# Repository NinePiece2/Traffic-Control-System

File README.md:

# **Traffic Control System** 🚦  

## NOTE

This project has been archived and all deployments have been termianted. 
If you want to deploy the project use the docker compose file.

## Table of Contents
- [**Traffic Control System** 🚦](#traffic-control-system-)
  - [Table of Contents](#table-of-contents)
  - [Workflow Status](#workflow-status)
  - [Introduction \& Background](#introduction--background)
    - [Background](#background)
    - [Rationale](#rationale)
    - [Scope](#scope)
  - [Design Specifications](#design-specifications)
    - [Pedestrian Detection and Safety](#pedestrian-detection-and-safety)
    - [Real-Time Video Streaming](#real-time-video-streaming)
    - [Hand Drawn Schematic of the Physical Design](#hand-drawn-schematic-of-the-physical-design)
    - [Microservice Architecture Design Diagram](#microservice-architecture-design-diagram)
    - [Early Design Mockup](#early-design-mockup)
    - [Final Design Implementation](#final-design-implementation)
      - [User Login](#user-login)
      - [Available Signals](#available-signals)
      - [Incident Reports for a Traffic Light](#incident-reports-for-a-traffic-light)
      - [Live Traffic Light](#live-traffic-light)
      - [Accounts Page](#accounts-page)
    - [Physical Design Components](#physical-design-components)
      - [PCB Design Image](#pcb-design-image)
      - [Design Assembly Render](#design-assembly-render)
      - [Design Assembly Render Video](#design-assembly-render-video)
      - [Physical Design Photo](#physical-design-photo)
  - [Installing the Microservices](#installing-the-microservices)
  - [Client Install Instructions:](#client-install-instructions)
    - [Client Debugging](#client-debugging)

## Workflow Status

| Workflow | Status |
|----------|--------|
| CI MVC Application | |
| CI API Application |  |
| CI Video Application |  |
| CD MVC, API, and Video Applications |  |
| Client CI Pipeline |  |

## Introduction & Background

A **smart traffic control system** designed to efficiently manage and optimize traffic flow.

### Background
In the modern day, successfully controlling urban traffic in the city is a necessity due to the ever-increasing number of vehicles and, consequently, the need for pedestrian safety.  In considering the traffic control system, what comes to mind is its ability to handle complex, changing traffic conditions, communicate clearly, and be accessible to visually impaired pedestrians. Additionally, incorporating sophisticated monitoring and control features into these systems continues to pose a technical challenge.

A frequent drawback in previous designs was the dependence on RF-link communication, which imposed limitations regarding data transmission reliability and scalability. To overcome these limitations, this project shifts to utilizing WiFi communication, providing increased flexibility, greater bandwidth, and improved compatibility with contemporary web-oriented control systems.

### Rationale
When determining the core processing unit, the Raspberry Pi was selected with the vision of being capable of employing adaptable and affordable embedded systems. Some of the benefits of the Raspberry Pi include real-time data processing, streamlined integration with cameras and sensors, and effective communication through WiFi. This makes it a perfect option for projects that need both hardware management and software interaction.

The web technologies were chosen to offer an intuitive user interface for system supervision and management. A .NET MVC website was created, incorporating Microsoft Identity Framework for secure user login, allowing the traffic system managers to have remote access to the system. As a result, supervisors can easily change parameters, manually control traffic signals, and view stored camera data such as images and videos of traffic violations. The addition of video imaging features improves the dependability of the system by allowing for future footage examination, holding violators accountable.

### Scope
The prototype created in this project tackles essential elements of traffic management by emphasizing real-time regulation and accessibility components. The system comprises:

1.	Real-Time Traffic Management: Combining magnetic reed switches and pedestrian buttons enables adaptive modification of traffic signals according to the presence of vehicles and pedestrians.
2.	Pedestrian Support: Buttons to signal a pedestrian to cross safely. Additionally, chimes at the time of safe crossing to signal the visually impaired are included.
3.	Traffic Violation Surveillance: A CMOS camera records high-quality images of traffic infractions, with video recording capabilities available for immediate processing and storage.
4.	Remote Management: A prototype website, developed using .NET MVC, allows for secure manual traffic light operations and remote observation of violation information.

This project provides a scalable solution for traffic control issues by incorporating contemporary technologies and enhancing traditional models. Future versions can upgrade the system’s capabilities to incorporate sophisticated image recognition, cloud storage, and overall traffic management across the network.

---

## Design Specifications

The Traffic Light Control System is designed to improve traffic management and pedestrian safety while addressing modern urban mobility challenges. The system provides:
-	Accessibility for Visually Impaired Pedestrians: Auditory signals inform visually impaired individuals when it is safe to cross the street.
-	Traffic Violation Detection: The Traffic Light Control System uses pressure sensors in order to detect when a vehicle crosses an intersection under a red light. It also uses a camera to take a picture of the violator's license plate, and record it for further use.
-	Remote Control and Data Access: The system uses a user friendly GUI, which, when connected to the internet, allows for monitoring the intersection at real time. Other features include recording and storing violations, and also manually adjusting the lights using an override.
-	Operation Modes: The user can change  traffic signal timings in accordance to different times of the day. this is useful for when there is an unexpected scenario, or an increase or decrease in traffic.
-	Power and Processing Requirements: A 5V power supply supports a Raspberry Pi single-board computer. The Raspberry Pi's integrated GPIO pins are used to interface with sensors, cameras, and traffic signal components, making it a very easy to use platform for this application.

### Pedestrian Detection and Safety

The SSD-MobileNetV2-FPNLite model is used to properly identify and classify pedestrians, vehicles and other objects. Pytesseract is used to extract license plates from vehicles that have commited traffic violations. For pedestrian safety, buzzers are used to sound for when there is a traffic violation detected, which is used alongside a pressure sensor. Lastly, other audio beeps are used for when a pedestrian requests to cross, and then they are sounded to make both the pedestrian and driver alerted of the shortened signal timings.

### Real-Time Video Streaming

RTMP ensures smooth video streaming from the CMOS camera to the GUI. This allows the user to be able to control traffic remotely, and make any changes necessary. They can also monitor the live intersection, and look at recorded traffic violations, should they deem necessary.

### Hand Drawn Schematic of the Physical Design

### Microservice Architecture Design Diagram

.png)

### Early Design Mockup

### Final Design Implementation

#### User Login 

#### Available Signals

#### Incident Reports for a Traffic Light

#### Live Traffic Light

#### Accounts Page

### Physical Design Components

To make the physical design look cohesive, a custom Printed Circut Board was designed and manufactured to replicate an actual traffic light. The CAD and PCB design files are availabe <a href="https://github.com/NinePiece2/Traffic-Control-System/tree/master/CADFiles" target="_blank" rel="noopener noreferrer">here</a>. The CAD files were designed using Fusion 360 and the PCB was created using KiCAD.

#### PCB Design Image

#### Design Assembly Render

#### Design Assembly Render Video

<!-- <video src="images/Dual_Traffic_Light_Variant_2_Assembly_Render_v3_Animation_2.mp4" autoplay muted loop playsinline width="800"></video> -->

Click to download the video:

#### Physical Design Photo

---

## Installing the Microservices

Use ```docker-compose.yml``` and change the variables where applicable to allow the microservices to communicate with each other. Use SSL certificates as required. The `JWT_KEY` should be the same on all the services.

```docker-compose.yml```:

```yml
version: '3.8'

services:
  mvc:
    image: ninepiece2/traffic-control-system:mvc
    container_name: Traffic-Control-System
    ports:
      - "8443:8443"
    volumes:
      - /root/certs:/https:ro
    environment:
      - ASPNETCORE_URLS=https://*:8443;http://*:8080
      - ASPNETCORE_Kestrel__Certificates__Default__Path=/https/ssl.crt
      - ASPNETCORE_Kestrel__Certificates__Default__KeyPath=/https/ssl.key
      - ASPNETCORE_ENVIRONMENT=${ASPNETCORE_ENVIRONMENT}
      - SyncfusionLicense=${SyncfusionLicense}
      - BaseUrl=https://trafficcontrolsystem.romitsagu.com
      - VideoServiceURL=https://stream-trafficcontrolsystem.romitsagu.com
      - StreamServiceURL=https://stream1-trafficcontrolsystem.romitsagu.com
      - APIURL=https://api-trafficcontrolsystem.romitsagu.com
      - API_KEY=${JWT_Key}
    command: ["dotnet", "Traffic-Control-System.dll"]
    restart: always
  
  api:
    image: ninepiece2/traffic-control-system:api
    container_name: Traffic-Control-System-API
    ports:
      - "8445:8445"
    volumes:
      - /root/certs:/https:ro
    environment:
      - ASPNETCORE_URLS=https://*:8445;http://*:8080
      - ASPNETCORE_Kestrel__Certificates__Default__Path=/https/ssl.crt
      - ASPNETCORE_Kestrel__Certificates__Default__KeyPath=/https/ssl.key
      - ASPNETCORE_ENVIRONMENT=${ASPNETCORE_ENVIRONMENT}
      - StreamServiceURL=https://stream1-trafficcontrolsystem.romitsagu.com
      - JWT:Issuer=https://api-trafficcontrolsystem.romitsagu.com
      - JWT:Audience=https://api-trafficcontrolsystem.romitsagu.com
      - JWT:Key=${JWT_Key}
    command: ["dotnet", "Traffic-Control-System-API.dll"]
    restart: always

  video:
    image: ninepiece2/traffic-control-system:video
    container_name: Traffic-Control-System-Video
    ports:
      - "1935:1935"
      - "8446:8446"
    volumes:
      - /root/certs:/https:ro
    environment:
      - ASPNETCORE_URLS=https://*:8446;http://*:8080
      - ASPNETCORE_Kestrel__Certificates__Default__Path=/https/ssl.crt
      - ASPNETCORE_Kestrel__Certificates__Default__KeyPath=/https/ssl.key
      - ASPNETCORE_ENVIRONMENT=${ASPNETCORE_ENVIRONMENT}
      - JWT:Issuer=https://stream-trafficcontrolsystem.romitsagu.com
      - JWT:Audience=https://stream-trafficcontrolsystem.romitsagu.com
      - JWT:Key=${JWT_Key}
    command: ["dotnet", "Traffic-Control-System-Video.dll"]
    restart: always
```

## Client Install Instructions:

Run the following on a Raspberry Pi 5. This will install docker, docker compose and create a new folder with the ```docker-compose.yml``` file and a config file located under ```config/config.json```. After creating a new traffic light in the MVC application enter the outputed config values in the ```config/config.json``` file. Follow the instructions and run ```docker compose up -d```/```docker-compose up -d``` within the created folder to run the container and traffic light application.

```sh
curl -O https://raw.githubusercontent.com/NinePiece2/Traffic-Control-System/refs/heads/master/RaspPiPythonScripts/installer.sh && sudo bash installer.sh
```

### Client Debugging

If you enconuter:

```sh
OSError: [Errno 12] Cannot allocate memory
```

Go to the file `sudo nano /boot/firmware/config.txt`

Locate the line `dtoverlay=vc4-fkms-v3d` and change it to `dtoverlay=vc4-fkms-v3d,cma-256` and Restart the Raspberry Pi.

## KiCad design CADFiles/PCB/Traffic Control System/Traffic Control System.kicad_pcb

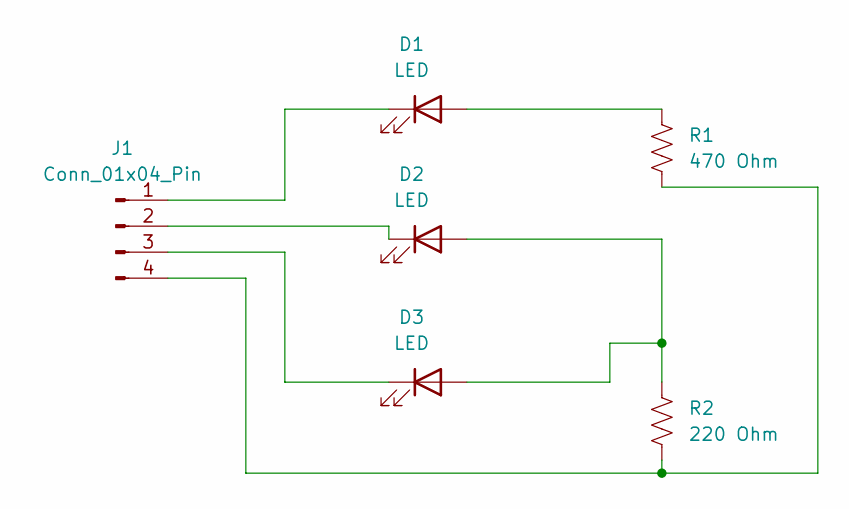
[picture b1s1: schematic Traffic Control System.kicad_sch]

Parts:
D1, D2, D3: LED; LED_D5.0mm_Clear
J1: Conn_01x04_Pin; SolderWire-0.25sqmm_1x04_P4.2mm_D0.65mm_OD1.7mm
R1: 470 Ohm; R_Box_L13.0mm_W4.0mm_P9.00mm
R2: 220 Ohm; R_Box_L13.0mm_W4.0mm_P9.00mm

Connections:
unnamed: D1.2 (A), R1.1
unnamed: D1.1 (K), J1.1
unnamed: D2.2 (A), D3.2 (A), R2.1
unnamed: D2.1 (K), J1.2
unnamed: D3.1 (K), J1.3
unnamed: J1.4, R1.2, R2.2

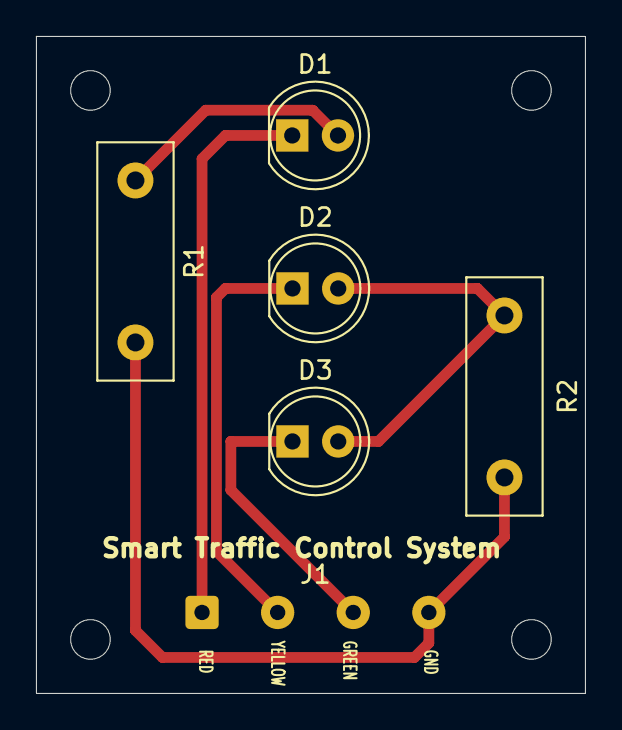
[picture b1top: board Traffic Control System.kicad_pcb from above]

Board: 2 copper layers, 30.5 x 36.5 mm, 6 parts (0 on the bottom side), 6 nets.

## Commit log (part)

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2024-10-03 Add .gitattributes and .gitignore.
2024-10-03 Add project files.
2024-10-03 Adding CI/CD
2024-10-03 Connect DB
2024-10-04 add README.md
2024-10-05 Small Changes
2024-10-05 Add Syncfusion and Admin Page
2024-10-06 Fix up admin users page
2024-10-08 Small Login Page Fixes
2024-10-09 Update Secondary Colour
2024-10-09 Add PowerSettings
2024-10-10 Add Email Service
2024-10-11 Add Confirmed User accounts and more Email Service Functionality
2024-10-12 Add approval/deny UI
2024-10-14 Add account approved logic
2024-10-16 Add Role Changes
2024-10-18 UI Improvements
2024-10-18 UI Improvements and Register Page Validation fixes
2024-10-18 Navbar Enhancements
2024-10-25 Add pi python test file
2024-10-25 Fix basic traffic light setup
2024-10-27 Add Websocket and video test
2024-10-27 Fix video issues
2024-10-27 add creations to dockerfile
2024-10-27 Try fix
2024-10-27 Add wget
2024-10-27 Try fix docker setup
2024-10-27 Try fix docker
2024-10-27 Fix docker
2024-10-27 Try to improve delay
2024-10-27 try to fix framerate
2024-10-27 Try to fix delay
2024-10-27 Try to fix framerate issues
2024-10-31 Use LiveStreamingServerNet for video streaming.
2024-10-31 Add python video streaming
2025-01-03 Add Seperate Microservices
2025-01-03 Fix build issues
2025-01-03 Try to fix publish
2025-01-03 Prune Images upon creation
2025-01-03 Try to fix build/publish issue
2025-01-03 Try to fix build/puiblsih
2025-01-03 Add missing file
2025-01-04 Try to fix video FFMpeg error
2025-01-08 Fix video streaming server
2025-01-12 Update URLs add add ClipController
2025-01-12 Update URLs
2025-01-13 Add Video Player demo
2025-01-13 Improved stream and video recording
2025-01-13 Add updated video stream
2025-01-13 Add initial FTP File Service
2025-01-13 Updated: The Signals Page
2025-01-14 Update ActiveSignals to use View TrafficSignals instead
2025-01-14 Update Video and MVC services
2025-01-16 Update .gitignore [no-ci]
2025-01-16 Make Clip Storage dependant on intersection
2025-01-16 Fix video upload issue
2025-01-16 Add Clips Uploader
2025-01-18 signalR test
2025-01-18 Add SignalR source
2025-01-18 python client for getting StreamClientKey using GET
2025-01-19 python client for get requests and StreamClientKey
2025-01-19 removal of file
2025-01-20 c# code for post requests and subsequent python code
2025-01-20 c# code for post requests and subsequent working python code
2025-01-20 Add Arshad Changes
2025-01-21 Fix Py Issue [no ci]
2025-01-22 Updateone
2025-01-22 Update Modal/Pop-Up
2025-01-23 Add Frontend for Video Streaming and Clip Viewing
2025-01-23 Fix SignalR merge issue
2025-01-23 Add Page Links
2025-01-29 Add Python Compose update
2025-01-29 Update python ci
2025-01-29 Fix and Test python CI
2025-01-30 Small Changes [no-ci]
2025-01-30 Update docker file for testing and installer
2025-01-30 Fix requirements
2025-01-30 Fix lgpio issue
2025-01-30 Fix gpiozero issue
2025-01-30 Fix Docker runtime issue
2025-01-30 Update Python Library
2025-01-30 Add missing requirements
2025-01-30 Add Webcam config
2025-01-31 Try to fix webcam issue
2025-01-31 Try to fix FFMpeg issue
2025-01-31 Try to fix FFMpeg Webcam issue
2025-01-31 Update [skip ci]
2025-01-31 Add manual CI option
2025-01-31 Fix CI picamera2 install issue
2025-01-31 Fix numpy dependency issue
2025-01-31 Update docker-compose.yml [skip ci]
2025-01-31 Clean up repos [skip ci]
2025-02-02 Small Update [skip ci]
2025-02-02 Update installer [skip ci]
2025-02-03 Fix Installer
2025-02-03 Fix Installer [skip ci]
2025-02-03 signal r update
2025-02-04 Update SignalR Receive message [skip ci]
2025-02-07 updating modal
2025-02-07 updateeee
2025-02-11 Edit table update
2025-02-11 Updated Index
2025-02-13 traffic controller for direction and time and python client
2025-02-13 traffic controller for direction and time and python client without bloat
2025-02-13 traffic controller for direction and time and python client without bloat updated
2025-02-13 removed dist
2025-02-13 Try to fix concurrent CI issue
2025-02-17 Add YOLO
2025-02-17 Use IMX500
2025-02-17 Update IMX500
2025-02-17 Update video
2025-02-17 Add IMX500 Object Detection and Test CI
2025-02-17 Remove unneeded entry in .gitignore
2025-02-17 Try to fix pip install issue
2025-02-18 Add Incident Detected Hook
2025-02-18 Add Table Of Contents
2025-02-18 README.md update
2025-02-18 Try to fix build error
2025-02-18 Client Update [skip ci]
2025-02-18 Add License Plate Detection
2025-02-18 Fix assets path
2025-02-18 Impove License Plate Detection
2025-02-18 Improve Clip Capture
2025-02-18 Add Tesseract OCR
2025-02-18 Fix folder upload
2025-02-18 Add Improve CI/CD for improved runtime
2025-02-18 Fix version issue
2025-02-18 Fix Pipeline README.md information
2025-02-18 Fix Video Framerate issue [skip ci]
2025-02-19 Improve Incident Reports Page
2025-02-19 UI Updates
2025-02-19 Add Filtering to Index
2025-02-19 Add Filtering and Sorting to Index Table
2025-02-19 Add Latest Violation
2025-02-22 Don't upload the original video
2025-02-22 Add better video autoplay and video sizing
2025-02-22 Try to fix unified deploy issue
2025-02-22 Try to fix deploy concurrency issue
2025-02-22 Improve Reports page videos
2025-02-23 Add persistant key database storage
2025-02-23 Remove unneeded import [skip ci]
2025-03-05 Final Update:
2025-03-06 Fix API Key issue [skip ci]
2025-03-06 Add PCB Files
2025-03-06 Add Gerber Output Files
2025-03-07 Update PCB
2025-03-07 Add Traffic Light Stand .step files
2025-03-08 Update GetDirectionAndTime()
2025-03-08 Add PedestrianWalkTime to API
2025-03-08 Add final PCB Fabrication Files
2025-03-10 Client Changes [skip ci]
2025-03-10 Update Device Control [skip ci]
2025-03-10 Update Server and Client SignalR Interfaces
2025-03-10 Update SignalR Server
2025-03-10 Add traffic light status passthrough
2025-03-10 Fix Colour Case Issue
2025-03-10 Use Classes Instead of IDs for timing spans
2025-03-10 Make SignalR connection more reliable
2025-03-10 Remove Unneded Comments
2025-03-10 Try to fix excesive console logs
2025-03-10 Improve UI/UX
2025-03-10 Add Buzzers and Revise Buttons [skip ci]
2025-03-10 Update Pedestrian Buttons [skip ci]
2025-03-10 Set Duy Cycle to 20% [skip ci]
2025-03-10 Update Buzzer and Pedestrian Logic [skip ci]
2025-03-10 Update Pedestrian Sounds
2025-03-11 Add missing method
2025-03-11 Fix Jingle Sounds
2025-03-11 Improve Buzzer Initialization [skip ci]
2025-03-11 Improve Buzzer Timings [skip ci]
2025-03-11 Add Button and Buzzer Stand
2025-03-11 Remove Unneeded Pages
2025-03-12 Update CAD Files
2025-03-13 Small Updates [skip ci]
2025-03-14 Add pressure sensing [skip ci]
2025-03-14 Fix double pin issue [skip ci]
2025-03-14 Add Getting Buzzer Volume and adding it tothe config
2025-03-14 Add Incident Detection [skip ci]
2025-03-14 Try to fix FFMpeg Issue [skip ci]
2025-03-14 Improve Pedestrian Button Mount
2025-04-04 Fix timing bug
2025-08-12 Add documentation
2025-08-13 Improve design specs
2025-09-23 Upgrade .NET SDK and runtime to version 9.0 across all projects and update dependencies
2025-09-23 Update workflow configurations to use 'ubuntu-latest' instead of 'self-hosted'
2025-09-23 deps(github-actions): bump docker/build-push-action from 5 to 6
    Bumps [docker/build-push-action](https://github.com/docker/build-push-action) from 5 to 6.
    - [Release notes](https://github.com/docker/build-push-action/releases)
    - [Commits](https://github.com/docker/build-push-action/compare/v5...v6)
    ---
    updated-dependencies:
    - dependency-name: docker/build-push-action
2025-09-23 deps(github-actions): bump actions/github-script from 6 to 8
    Bumps [actions/github-script](https://github.com/actions/github-script) from 6 to 8.
    - [Release notes](https://github.com/actions/github-script/releases)
    - [Commits](https://github.com/actions/github-script/compare/v6...v8)
    ---
    updated-dependencies:
    - dependency-name: actions/github-script
2025-10-01 deps(github-actions): bump peter-evans/repository-dispatch from 3 to 4
    Bumps [peter-evans/repository-dispatch](https://github.com/peter-evans/repository-dispatch) from 3 to 4.
    - [Release notes](https://github.com/peter-evans/repository-dispatch/releases)
    - [Commits](https://github.com/peter-evans/repository-dispatch/compare/v3...v4)
    ---
    updated-dependencies:
    - dependency-name: peter-evans/repository-dispatch
2025-11-20 deps(github-actions): bump actions/checkout from 5 to 6
    Bumps [actions/checkout](https://github.com/actions/checkout) from 5 to 6.
    - [Release notes](https://github.com/actions/checkout/releases)
    - [Changelog](https://github.com/actions/checkout/blob/main/CHANGELOG.md)
    - [Commits](https://github.com/actions/checkout/compare/v5...v6)
    ---
    updated-dependencies:
2026-02-05 deps(Traffic-Control-System): Bump the microsoft-dependencies group with 8 updates
    Bumps Microsoft.AspNetCore.DataProtection.EntityFrameworkCore from 9.0.9 to 9.0.12
    Bumps Microsoft.AspNetCore.Diagnostics.EntityFrameworkCore from 9.0.9 to 9.0.12
    Bumps Microsoft.AspNetCore.Identity.EntityFrameworkCore from 9.0.9 to 9.0.12
    Bumps Microsoft.AspNetCore.Identity.UI from 9.0.9 to 9.0.12
    Bumps Microsoft.EntityFrameworkCore.Sqlite from 9.0.9 to 9.0.12
    Bumps Microsoft.EntityFrameworkCore.SqlServer from 9.0.9 to 9.0.12
2026-02-05 deps(Traffic-Control-System): Bump dotenv.net from 3.2.1 to 4.0.0
    ---
    updated-dependencies:
    - dependency-name: dotenv.net
    dependency-version: 4.0.0
    dependency-type: direct:production
    update-type: version-update:semver-major
2026-02-05 deps(Traffic-Control-System-API): Bump the microsoft-dependencies group with 9 updates
    Bumps Microsoft.AspNetCore.Authentication.JwtBearer from 9.0.9 to 9.0.12
    Bumps Microsoft.AspNetCore.DataProtection.EntityFrameworkCore from 9.0.9 to 9.0.12
    Bumps Microsoft.AspNetCore.Diagnostics.EntityFrameworkCore from 9.0.9 to 9.0.12
    Bumps Microsoft.AspNetCore.Identity.EntityFrameworkCore from 9.0.9 to 9.0.12
    Bumps Microsoft.AspNetCore.Identity.UI from 9.0.9 to 9.0.12
    Bumps Microsoft.EntityFrameworkCore.Sqlite from 9.0.9 to 9.0.12
2026-02-05 deps(Traffic-Control-System-API): Bump Swashbuckle.AspNetCore from 9.0.4 to 10.1.2
    ---
    updated-dependencies:
    - dependency-name: Swashbuckle.AspNetCore
    dependency-version: 10.1.2
    dependency-type: direct:production
    update-type: version-update:semver-major
2026-02-05 deps(Traffic-Control-System-Video): Bump FluentFTP from 53.0.1 to 53.0.2
    ---
    updated-dependencies:
    - dependency-name: FluentFTP
    dependency-version: 53.0.2
    dependency-type: direct:production
    update-type: version-update:semver-patch
2026-02-05 deps(Traffic-Control-System): Bump Syncfusion.EJ2.AspNet.Core from 27.1.51 to 32.2.3
    ---
    updated-dependencies:
    - dependency-name: Syncfusion.EJ2.AspNet.Core
    dependency-version: 32.2.3
    dependency-type: direct:production
    update-type: version-update:semver-major
2026-02-05 deps(Traffic-Control-System-Video): Bump LiveStreamingServerNet from 0.21.0 to 0.33.1
    ---
    updated-dependencies:
    - dependency-name: LiveStreamingServerNet
    dependency-version: 0.33.1
    dependency-type: direct:production
    update-type: version-update:semver-minor
2026-02-05 deps(Traffic-Control-System-Video): Bump LiveStreamingServerNet.Flv from 0.21.0 to 0.33.1
    ---
    updated-dependencies:
    - dependency-name: LiveStreamingServerNet.Flv
    dependency-version: 0.33.1
    dependency-type: direct:production
    update-type: version-update:semver-minor
2026-02-05 deps(Traffic-Control-System-Video): Bump LiveStreamingServerNet.Networking and LiveStreamingServerNet.Utilities
    Bumps LiveStreamingServerNet.Networking from 0.21.0 to 0.33.1
    Bumps LiveStreamingServerNet.Utilities from 0.21.0 to 0.33.1
    ---
    updated-dependencies:
    - dependency-name: LiveStreamingServerNet.Networking
    dependency-version: 0.33.1
